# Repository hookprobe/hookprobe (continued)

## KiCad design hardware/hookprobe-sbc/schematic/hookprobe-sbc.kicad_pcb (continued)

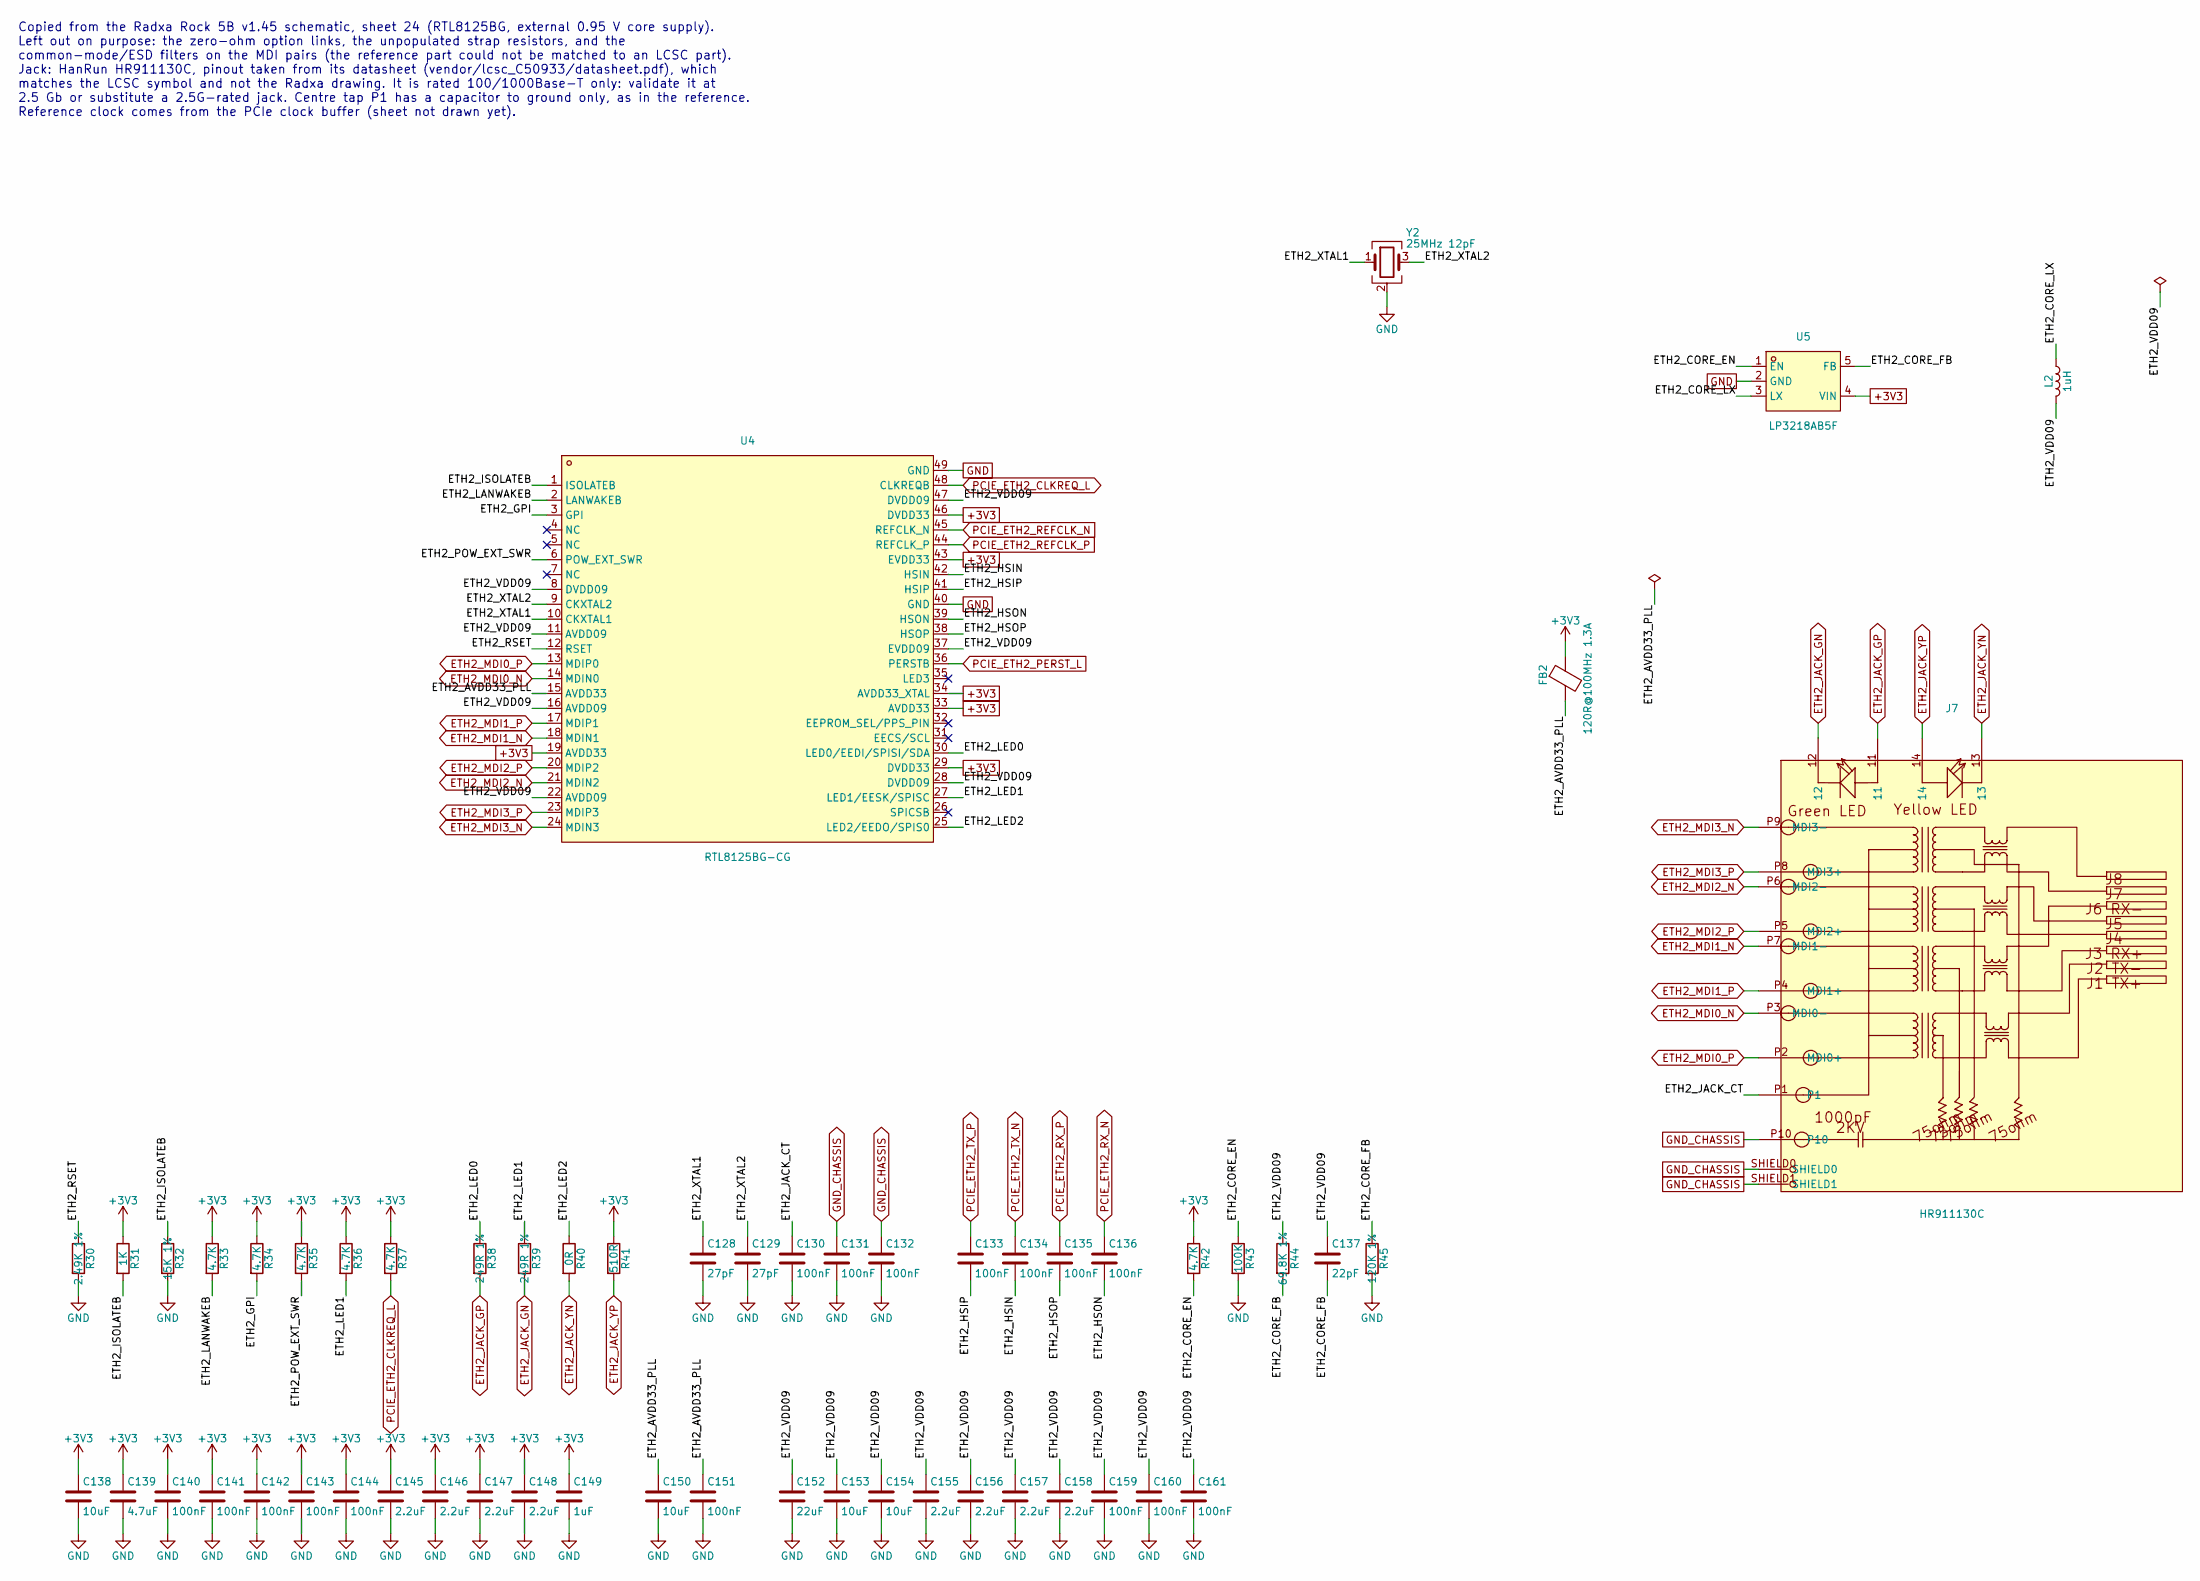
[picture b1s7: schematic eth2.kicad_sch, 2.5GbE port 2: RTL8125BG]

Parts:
C128, C129: 27pF; C_0402_1005Metric
C130, C131, C132, C133, C134, C135, C136, C140, C141, C142, C143, C144, C151, C159, C160, C161: 100nF; C_0402_1005Metric
C137: 22pF; C_0402_1005Metric
C138, C150, C153, C154: 10uF; C_0805_2012Metric
C139: 4.7uF; C_0805_2012Metric
C145, C146, C147, C148, C155, C156, C157, C158: 2.2uF; C_0402_1005Metric
C149: 1uF; C_0402_1005Metric
C152: 22uF; C_0805_2012Metric
FB2: 120R@100MHz 1.3A; L_0402_1005Metric; Part UPZ1005D121-1R3TF
J7: HR911130C; RJ45-TH_HR911130C; LCSC C50933
L2: 1uH; L_0805_2012Metric
R30: 2.49K 1%; R_0402_1005Metric
R31: 1K; R_0402_1005Metric
R32: 15K 1%; R_0402_1005Metric
R33, R34, R35, R36, R37, R42: 4.7K; R_0402_1005Metric
R38, R39: 249R 1%; R_0402_1005Metric
R40: 0R; R_0402_1005Metric
R41: 510R; R_0402_1005Metric
R43: 100K; R_0402_1005Metric
R44: 69.8K 1%; R_0402_1005Metric
R45: 120K 1%; R_0402_1005Metric
U4: RTL8125BG-CG; TQFN-48_L6.0-W6.0-P0.40-BL-EP4.5; LCSC C3013605
U5: LP3218AB5F; SOT-23-5_L2.9-W1.6-P0.95-LS2.8-BR; LCSC C517210
Y2: 25MHz 12pF; Crystal_SMD_3225-4Pin_3.2x2.5mm

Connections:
+3V3: C138.1, C139.1, C140.1, C141.1, C142.1, C143.1, C144.1, C145.1, C146.1, C147.1, C148.1, C149.1, FB2.1, R31.1, R33.1, R34.1, R35.1, R36.1, R37.1, R41.1, R42.1, U4.19 (AVDD33), U4.29 (DVDD33), U4.33 (AVDD33), U4.34 (AVDD33_XTAL), U4.43 (EVDD33), U4.46 (DVDD33), U5.4 (VIN); also elsewhere on the board
/2.5GbE port 2: RTL8125BG/ETH2_AVDD33_PLL: C150.1, C151.1, FB2.2, U4.15 (AVDD33)
/2.5GbE port 2: RTL8125BG/ETH2_CORE_EN: R42.2, R43.1, U5.1 (EN)
/2.5GbE port 2: RTL8125BG/ETH2_CORE_FB: C137.2, R44.2, R45.1, U5.5 (FB)
/2.5GbE port 2: RTL8125BG/ETH2_CORE_LX: L2.1, U5.3 (LX)
/2.5GbE port 2: RTL8125BG/ETH2_GPI: R34.2, U4.3 (GPI)
/2.5GbE port 2: RTL8125BG/ETH2_HSIN: C134.2, U4.42 (HSIN)
/2.5GbE port 2: RTL8125BG/ETH2_HSIP: C133.2, U4.41 (HSIP)
/2.5GbE port 2: RTL8125BG/ETH2_HSON: C136.2, U4.39 (HSON)
/2.5GbE port 2: RTL8125BG/ETH2_HSOP: C135.2, U4.38 (HSOP)
/2.5GbE port 2: RTL8125BG/ETH2_ISOLATEB: R31.2, R32.1, U4.1 (ISOLATEB)
/2.5GbE port 2: RTL8125BG/ETH2_JACK_CT: C130.1, J7.P1
/2.5GbE port 2: RTL8125BG/ETH2_LANWAKEB: R33.2, U4.2 (LANWAKEB)
/2.5GbE port 2: RTL8125BG/ETH2_LED0: R38.1, U4.30 (LED0/EEDI/SPISI/SDA)
/2.5GbE port 2: RTL8125BG/ETH2_LED1: R36.2, R39.1, U4.27 (LED1/EESK/SPISC)
/2.5GbE port 2: RTL8125BG/ETH2_LED2: R40.1, U4.25 (LED2/EEDO/SPIS0)
/2.5GbE port 2: RTL8125BG/ETH2_POW_EXT_SWR: R35.2, U4.6 (POW_EXT_SWR)
/2.5GbE port 2: RTL8125BG/ETH2_RSET: R30.1, U4.12 (RSET)
/2.5GbE port 2: RTL8125BG/ETH2_VDD09: C137.1, C152.1, C153.1, C154.1, C155.1, C156.1, C157.1, C158.1, C159.1, C160.1, C161.1, L2.2, R44.1, U4.8 (DVDD09), U4.11 (AVDD09), U4.16 (AVDD09), U4.22 (AVDD09), U4.28 (DVDD09), U4.37 (EVDD09), U4.47 (DVDD09)
/2.5GbE port 2: RTL8125BG/ETH2_XTAL1: C128.1, U4.10 (CKXTAL1), Y2.1
/2.5GbE port 2: RTL8125BG/ETH2_XTAL2: C129.1, U4.9 (CKXTAL2), Y2.3
ETH2_JACK_GN: J7.12, R39.2
ETH2_JACK_GP: J7.11, R38.2
ETH2_JACK_YN: J7.13, R40.2
ETH2_JACK_YP: J7.14, R41.2
ETH2_MDI0_N: J7.P3 (MDI0-), U4.14 (MDIN0)
ETH2_MDI0_P: J7.P2 (MDI0+), U4.13 (MDIP0)
ETH2_MDI1_N: J7.P7 (MDI1-), U4.18 (MDIN1)
ETH2_MDI1_P: J7.P4 (MDI1+), U4.17 (MDIP1)
ETH2_MDI2_N: J7.P6 (MDI2-), U4.21 (MDIN2)
ETH2_MDI2_P: J7.P5 (MDI2+), U4.20 (MDIP2)
ETH2_MDI3_N: J7.P9 (MDI3-), U4.24 (MDIN3)
ETH2_MDI3_P: J7.P8 (MDI3+), U4.23 (MDIP3)
GND: C128.2, C129.2, C130.2, C131.2, C132.2, C138.2, C139.2, C140.2, C141.2, C142.2, C143.2, C144.2, C145.2, C146.2, C147.2, C148.2, C149.2, C150.2, C151.2, C152.2, C153.2, C154.2, C155.2, C156.2, C157.2, C158.2, C159.2, C160.2, C161.2, R30.2, R32.2, R43.2, R45.2, U4.40 (GND), U4.49 (GND), U5.2 (GND), Y2.2 (G), Y2.4 (G); also elsewhere on the board
GND_CHASSIS: C131.1, C132.1, J7.P10, J7.SHIELD0, J7.SHIELD1; also elsewhere on the board
PCIE_ETH2_CLKREQ_L: R37.2, U4.48 (CLKREQB); also elsewhere on the board
PCIE_ETH2_PERST_L: U4.36 (PERSTB); also elsewhere on the board
PCIE_ETH2_REFCLK_N: U4.45 (REFCLK_N); also elsewhere on the board
PCIE_ETH2_REFCLK_P: U4.44 (REFCLK_P); also elsewhere on the board
PCIE_ETH2_RX_N: C136.1; also elsewhere on the board
PCIE_ETH2_RX_P: C135.1; also elsewhere on the board
PCIE_ETH2_TX_N: C134.1; also elsewhere on the board
PCIE_ETH2_TX_P: C133.1; also elsewhere on the board

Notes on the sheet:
Copied from the Radxa Rock 5B v1.45 schematic, sheet 24 (RTL8125BG, external 0.95 V core supply). Left out on purpose: the zero-ohm option links, the unpopulated strap resistors, and the common-mode/ESD filters on the MDI pairs (the reference part could not be matched to an LCSC part). Jack: HanRun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

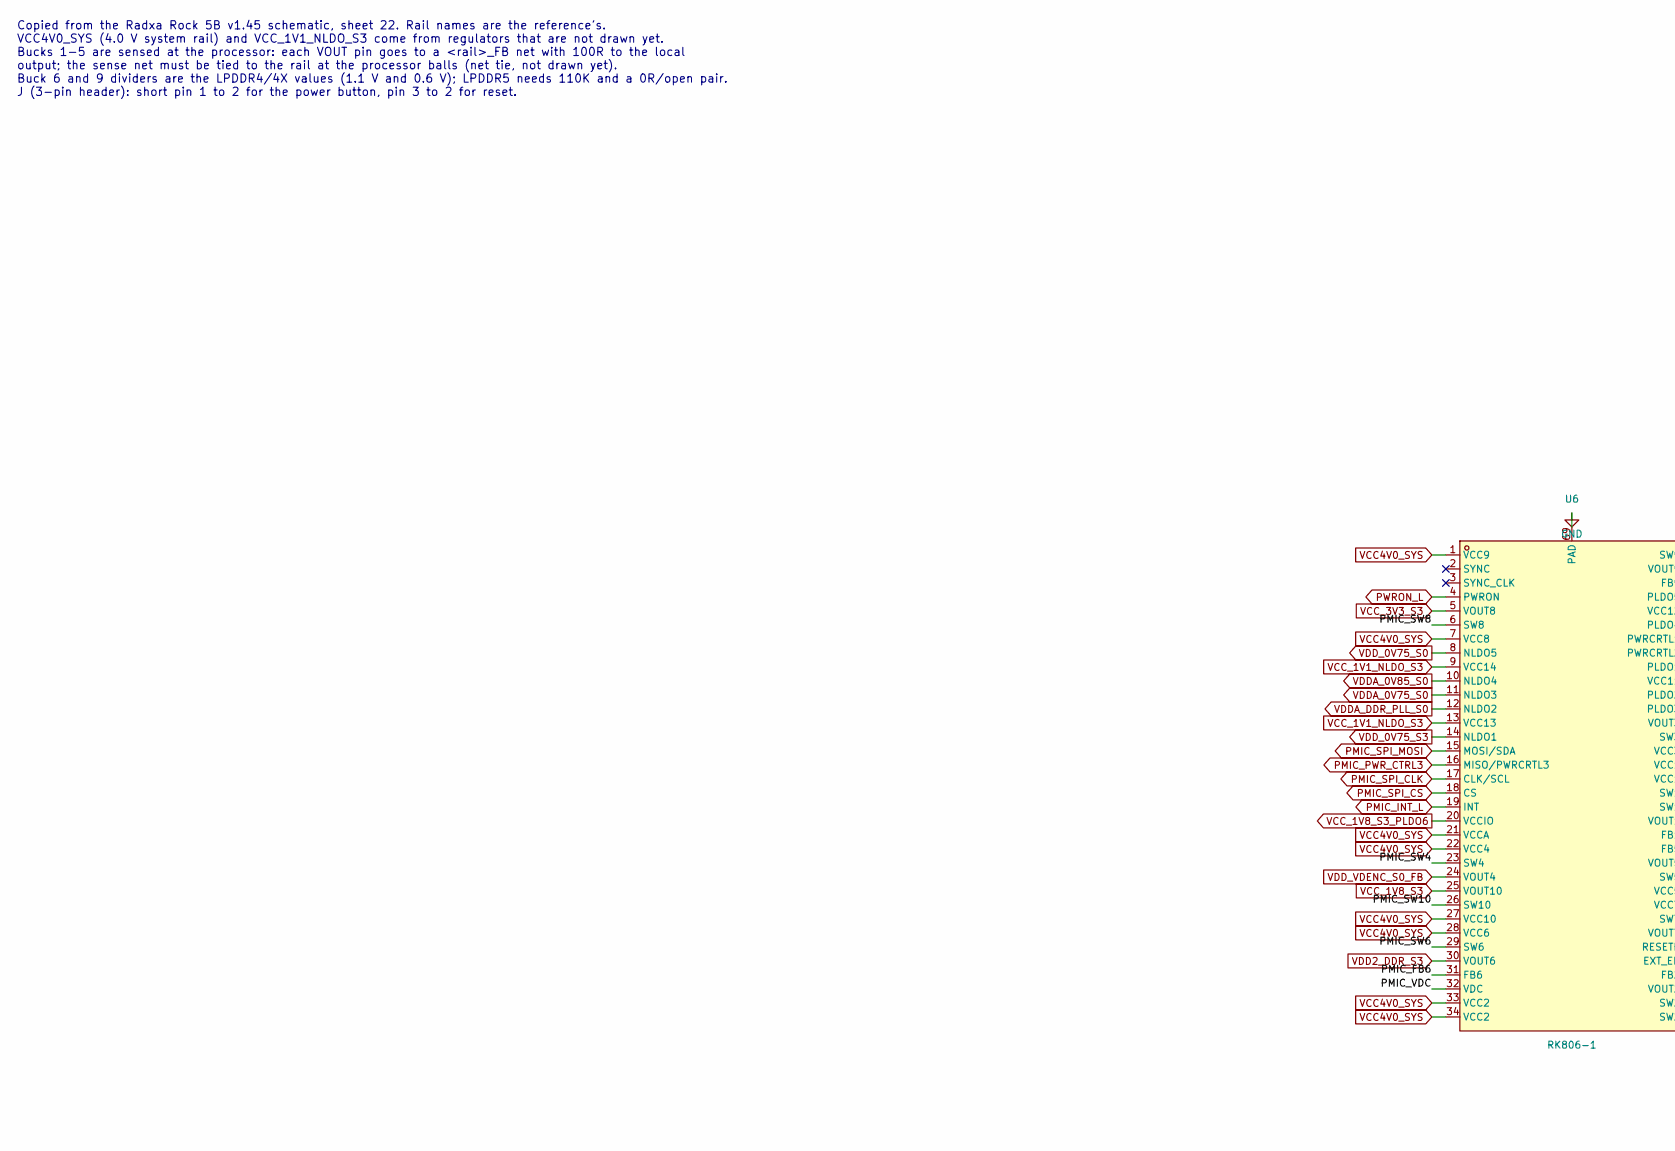
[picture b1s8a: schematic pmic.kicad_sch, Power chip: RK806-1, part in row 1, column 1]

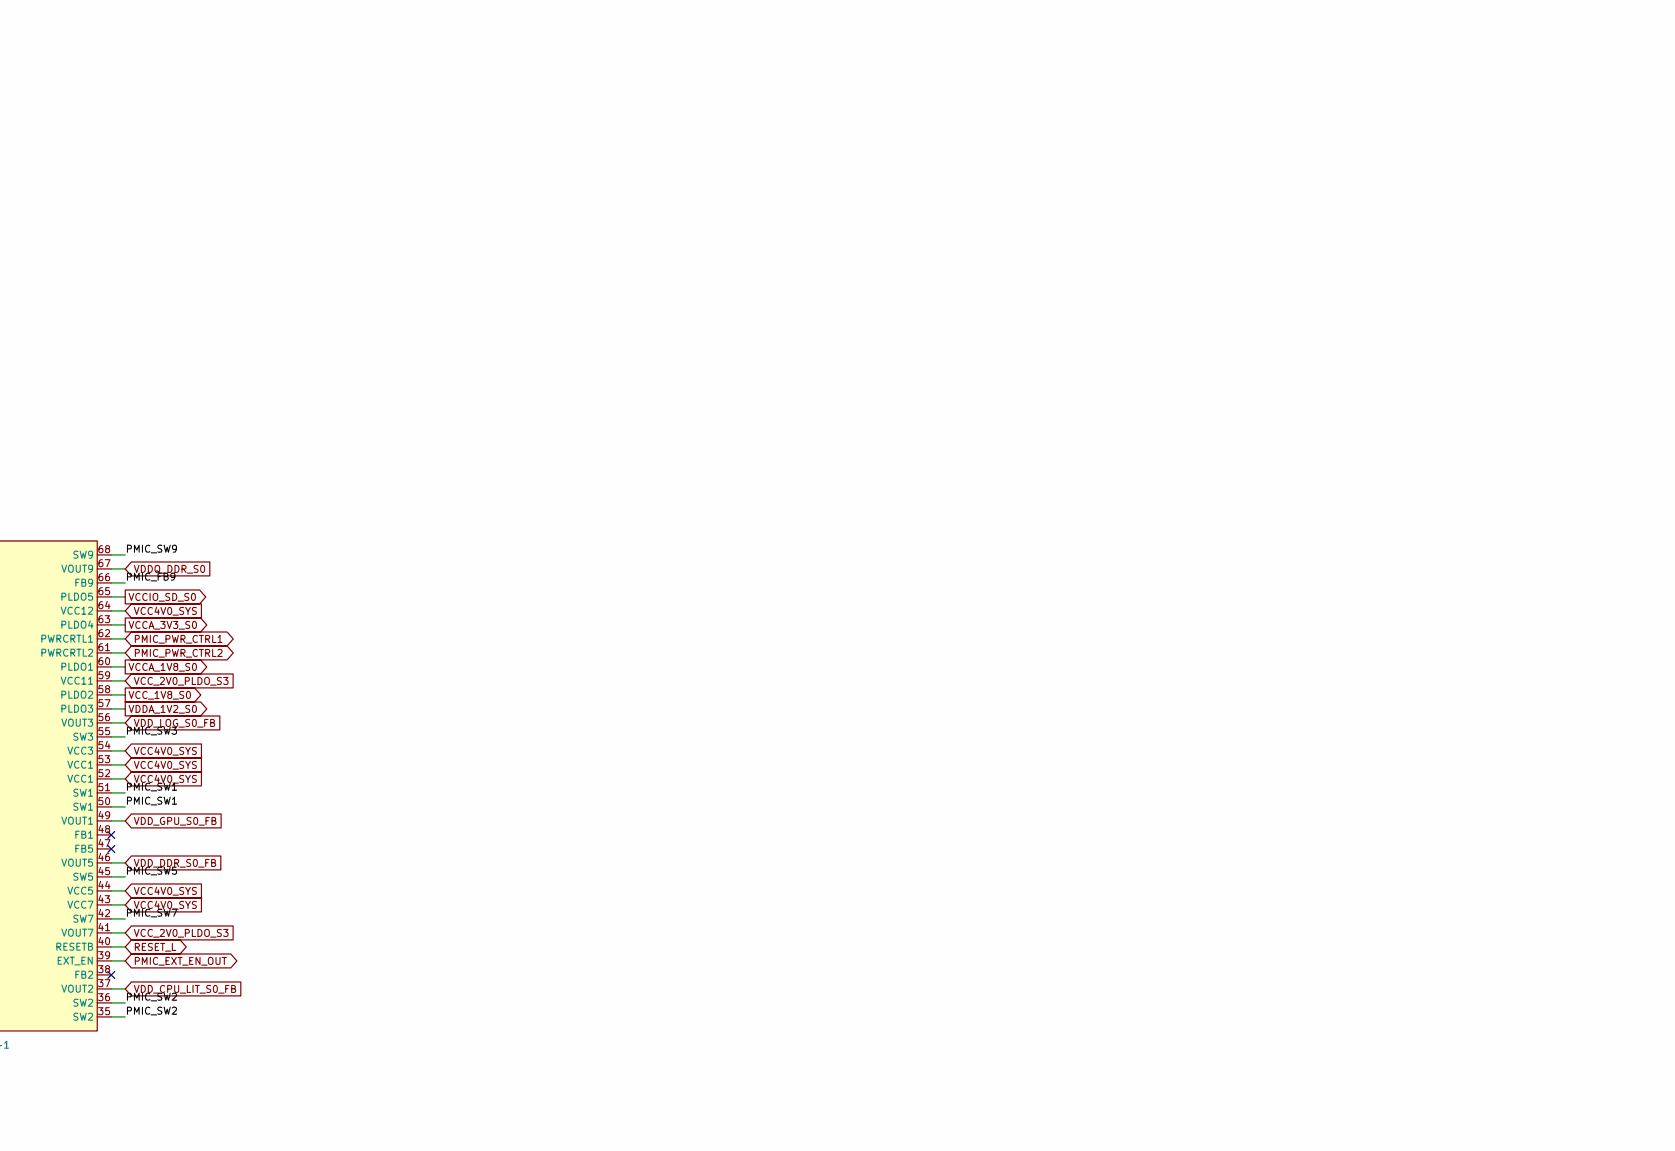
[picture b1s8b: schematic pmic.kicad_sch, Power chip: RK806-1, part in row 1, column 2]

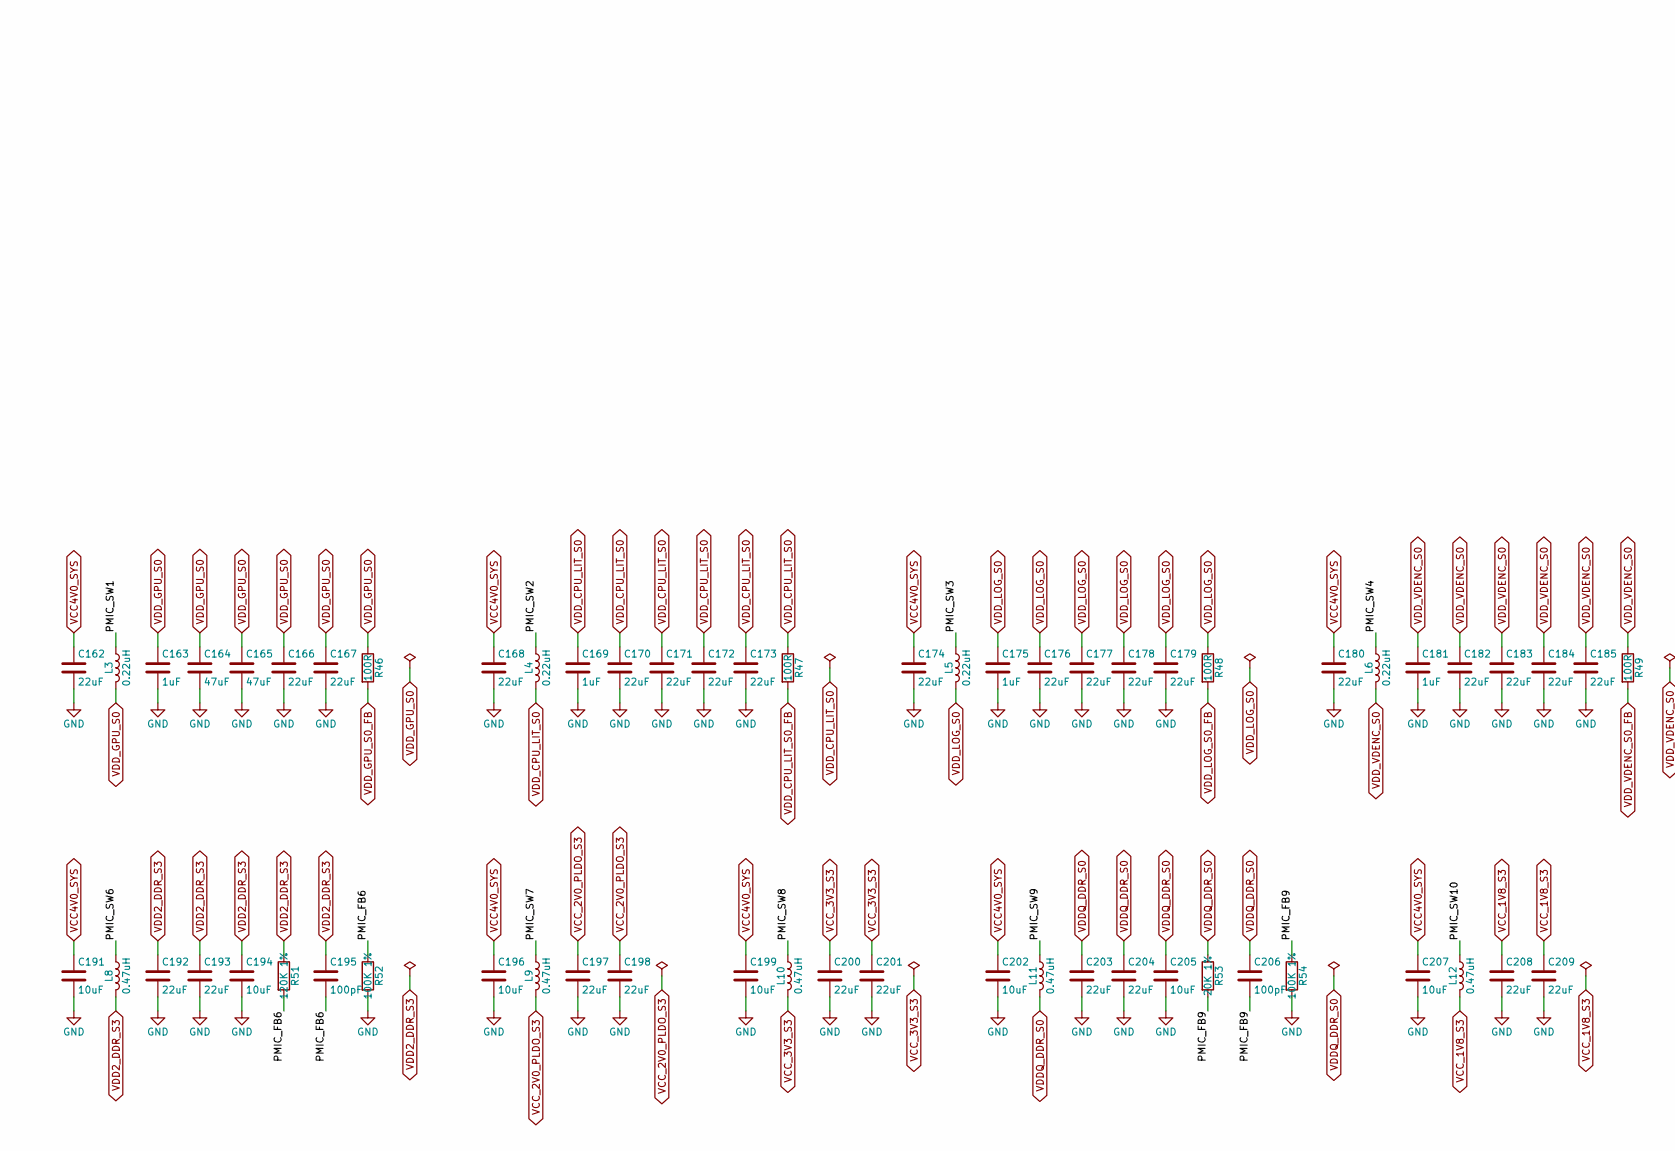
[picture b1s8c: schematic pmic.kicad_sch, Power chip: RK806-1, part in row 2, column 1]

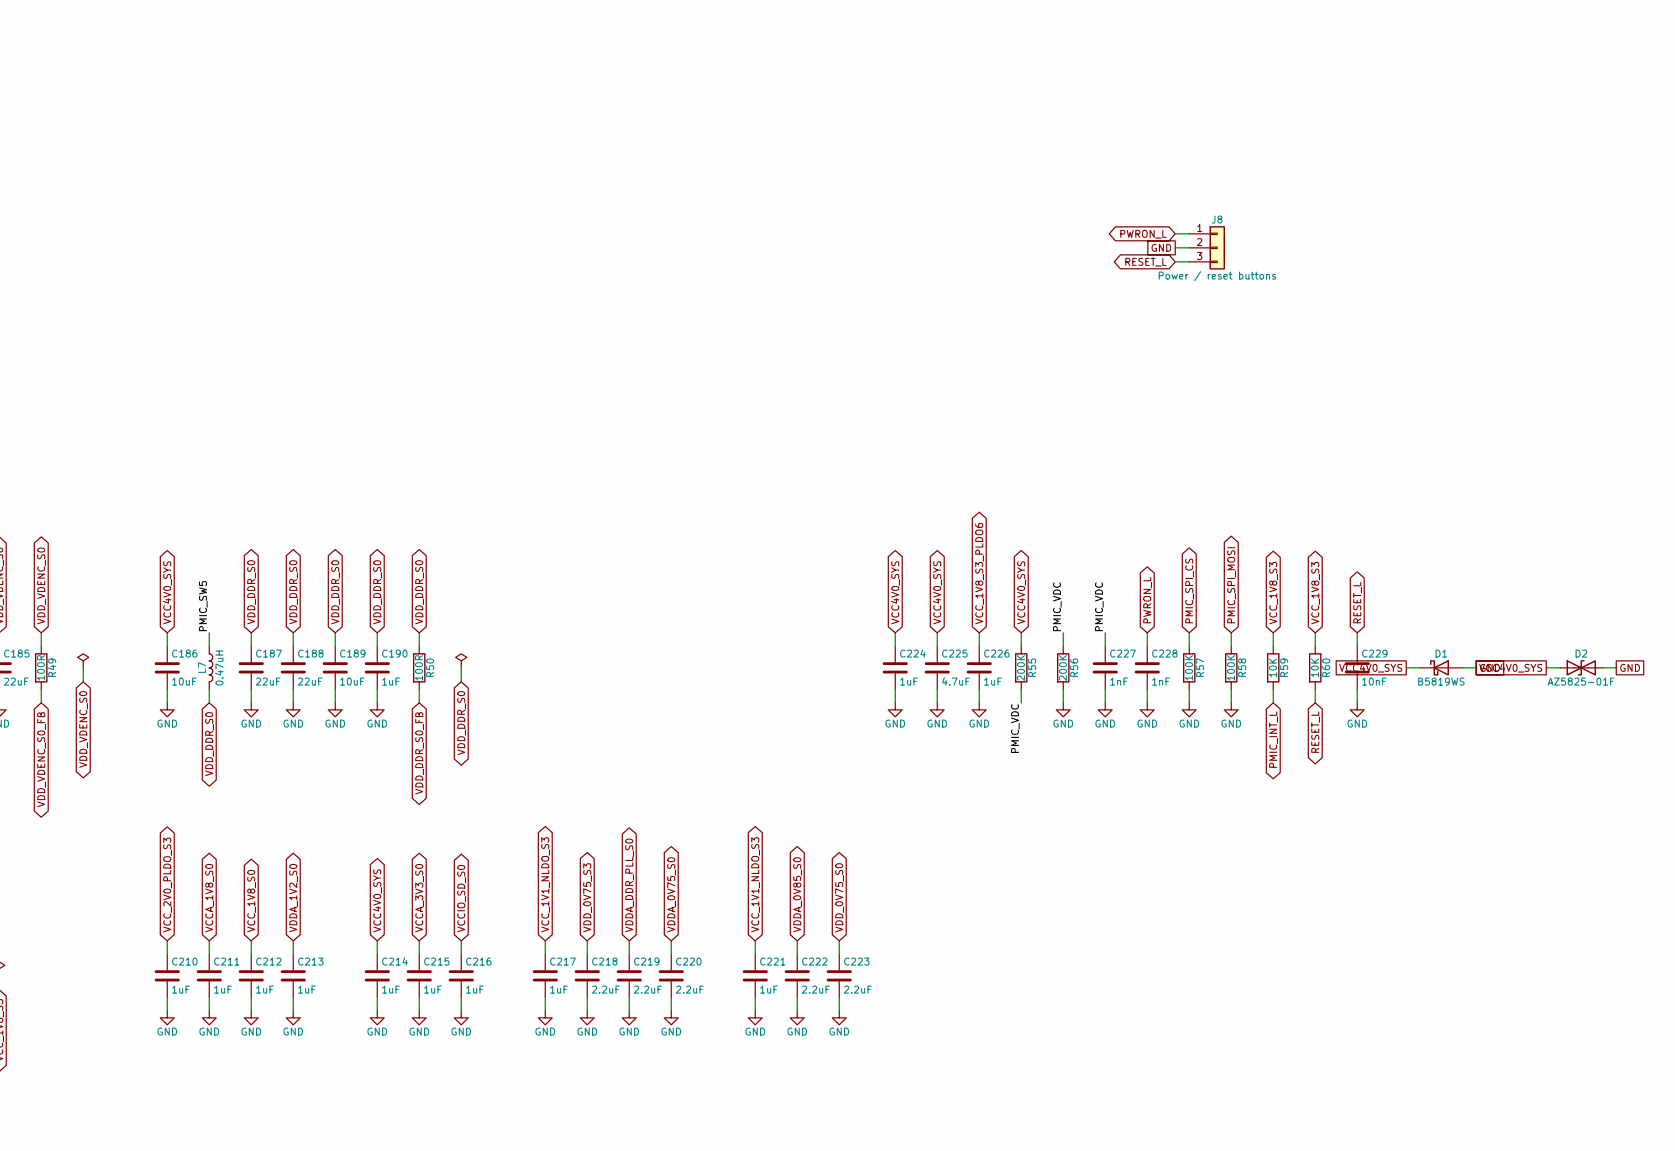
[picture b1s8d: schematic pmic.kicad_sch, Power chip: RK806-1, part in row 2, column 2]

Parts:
C162, C168, C174, C180: 22uF; C_0805_2012Metric
C163, C169, C175, C181, C190, C210, C211, C212, C213, C214, C215, C216, C217, C221, C224, C226: 1uF; C_0402_1005Metric
C164, C165: 47uF; C_0805_2012Metric
C166, C167, C170, C171, C172, C173, C176, C177, C178, C179, C182, C183, C184, C185, C187, C188, C192, C193, C197, C198, C200, C201, C203, C204, C208, C209: 22uF; C_0603_1608Metric
C186, C189, C191, C194, C196, C199, C202, C205, C207: 10uF; C_0603_1608Metric
C195, C206: 100pF; C_0402_1005Metric
C218, C219, C220, C222, C223: 2.2uF; C_0402_1005Metric
C225: 4.7uF; C_0402_1005Metric
C227, C228: 1nF; C_0402_1005Metric
C229: 10nF; C_0402_1005Metric
D1: B5819WS; D_SOD-323
D2: AZ5825-01F; D_0402_1005Metric
J8: Power / reset buttons; PinHeader_1x03_P2.54mm_Vertical
L3, L4, L5, L6: 0.22uH; L_1210_3225Metric
L7, L8, L9, L10, L11, L12: 0.47uH; L_1210_3225Metric
R46, R47, R48, R49, R50: 100R; R_0402_1005Metric
R51: 120K 1%; R_0402_1005Metric
R52, R54: 100K 1%; R_0402_1005Metric
R53: 20K 1%; R_0402_1005Metric
R55, R56: 200K; R_0402_1005Metric
R57, R58: 100K; R_0402_1005Metric
R59, R60: 10K; R_0402_1005Metric
U6: RK806-1; QFN-68_L7.0-W7.0-P0.35-BL-EP5.5; LCSC C5156483

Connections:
/Power chip: RK806-1/PMIC_FB6: C195.2, R51.2, R52.1, U6.31 (FB6)
/Power chip: RK806-1/PMIC_FB9: C206.2, R53.2, R54.1, U6.66 (FB9)
/Power chip: RK806-1/PMIC_SW1: L3.1, U6.50 (SW1), U6.51 (SW1)
/Power chip: RK806-1/PMIC_SW2: L4.1, U6.35 (SW2), U6.36 (SW2)
/Power chip: RK806-1/PMIC_SW3: L5.1, U6.55 (SW3)
/Power chip: RK806-1/PMIC_SW4: L6.1, U6.23 (SW4)
/Power chip: RK806-1/PMIC_SW5: L7.1, U6.45 (SW5)
/Power chip: RK806-1/PMIC_SW6: L8.1, U6.29 (SW6)
/Power chip: RK806-1/PMIC_SW7: L9.1, U6.42 (SW7)
/Power chip: RK806-1/PMIC_SW8: L10.1, U6.6 (SW8)
/Power chip: RK806-1/PMIC_SW9: L11.1, U6.68 (SW9)
/Power chip: RK806-1/PMIC_SW10: L12.1, U6.26 (SW10)
/Power chip: RK806-1/PMIC_VDC: C227.1, R55.2, R56.1, U6.32 (VDC)
GND: C162.2, C163.2, C164.2, C165.2, C166.2, C167.2, C168.2, C169.2, C170.2, C171.2, C172.2, C173.2, C174.2, C175.2, C176.2, C177.2, C178.2, C179.2, C180.2, C181.2, C182.2, C183.2, C184.2, C185.2, C186.2, C187.2, C188.2, C189.2, C190.2, C191.2, C192.2, C193.2, C194.2, C196.2, C197.2, C198.2, C199.2, C200.2, C201.2, C202.2, C203.2, C204.2, C205.2, C207.2, C208.2, C209.2, C210.2, C211.2, C212.2, C213.2, C214.2, C215.2, C216.2, C217.2, C218.2, C219.2, C220.2, C221.2, C222.2, C223.2, C224.2, C225.2, C226.2, C227.2, C228.2, C229.2, D1.2 (A), D2.2 (A2), J8.2, R52.2, R54.2, R56.2, R57.2, R58.2, U6.69 (PAD); also elsewhere on the board
PMIC_EXT_EN_OUT: U6.39 (EXT_EN); also elsewhere on the board
PMIC_INT_L: R59.2, U6.19 (INT); also elsewhere on the board
PMIC_PWR_CTRL1: U6.62 (PWRCRTL1); also elsewhere on the board
PMIC_PWR_CTRL2: U6.61 (PWRCRTL2); also elsewhere on the board
PMIC_PWR_CTRL3: U6.16 (MISO/PWRCRTL3); also elsewhere on the board
PMIC_SPI_CLK: U6.17 (CLK/SCL); also elsewhere on the board
PMIC_SPI_CS: R57.1, U6.18 (CS); also elsewhere on the board
PMIC_SPI_MOSI: R58.1, U6.15 (MOSI/SDA); also elsewhere on the board
PWRON_L: C228.1, J8.1, U6.4 (PWRON)
RESET_L: C229.1, J8.3, R60.2, U6.40 (RESETB); also elsewhere on the board
VCC4V0_SYS: C162.1, C168.1, C174.1, C180.1, C186.1, C191.1, C196.1, C199.1, C202.1, C207.1, C214.1, C224.1, C225.1, D1.1 (K), D2.1 (A1), R55.1, U6.1 (VCC9), U6.7 (VCC8), U6.21 (VCCA), U6.22 (VCC4), U6.27 (VCC10), U6.28 (VCC6), U6.33 (VCC2), U6.34 (VCC2), U6.43 (VCC7), U6.44 (VCC5), U6.52 (VCC1), U6.53 (VCC1), U6.54 (VCC3), U6.64 (VCC12); also elsewhere on the board
VCCA_1V8_S0: C211.1, U6.60 (PLDO1); also elsewhere on the board
VCCA_3V3_S0: C215.1, U6.63 (PLDO4); also elsewhere on the board
VCCIO_SD_S0: C216.1, U6.65 (PLDO5); also elsewhere on the board
VCC_1V1_NLDO_S3: C217.1, C221.1, U6.9 (VCC14), U6.13 (VCC13); also elsewhere on the board
VCC_1V8_S0: C212.1, U6.58 (PLDO2); also elsewhere on the board
VCC_1V8_S3: C208.1, C209.1, L12.2, R59.1, R60.1, U6.25 (VOUT10); also elsewhere on the board
VCC_1V8_S3_PLDO6: C226.1, U6.20 (VCCIO)
VCC_2V0_PLDO_S3: C197.1, C198.1, C210.1, L9.2, U6.41 (VOUT7), U6.59 (VCC11)
VCC_3V3_S3: C200.1, C201.1, L10.2, U6.5 (VOUT8); also elsewhere on the board
VDD2_DDR_S3: C192.1, C193.1, C194.1, C195.1, L8.2, R51.1, U6.30 (VOUT6); also elsewhere on the board
VDDA_0V75_S0: C220.1, U6.11 (NLDO3); also elsewhere on the board
VDDA_0V85_S0: C222.1, U6.10 (NLDO4); also elsewhere on the board
VDDA_1V2_S0: C213.1, U6.57 (PLDO3); also elsewhere on the board
VDDA_DDR_PLL_S0: C219.1, U6.12 (NLDO2); also elsewhere on the board
VDDQ_DDR_S0: C203.1, C204.1, C205.1, C206.1, L11.2, R53.1, U6.67 (VOUT9); also elsewhere on the board
VDD_0V75_S0: C223.1, U6.8 (NLDO5); also elsewhere on the board
VDD_0V75_S3: C218.1, U6.14 (NLDO1); also elsewhere on the board
VDD_CPU_LIT_S0: C169.1, C170.1, C171.1, C172.1, C173.1, L4.2, R47.1; also elsewhere on the board
VDD_CPU_LIT_S0_FB: R47.2, U6.37 (VOUT2); also elsewhere on the board
VDD_DDR_S0: C187.1, C188.1, C189.1, C190.1, L7.2, R50.1; also elsewhere on the board
VDD_DDR_S0_FB: R50.2, U6.46 (VOUT5); also elsewhere on the board
VDD_GPU_S0: C163.1, C164.1, C165.1, C166.1, C167.1, L3.2, R46.1; also elsewhere on the board
VDD_GPU_S0_FB: R46.2, U6.49 (VOUT1); also elsewhere on the board
VDD_LOG_S0: C175.1, C176.1, C177.1, C178.1, C179.1, L5.2, R48.1; also elsewhere on the board
VDD_LOG_S0_FB: R48.2, U6.56 (VOUT3); also elsewhere on the board
VDD_VDENC_S0: C181.1, C182.1, C183.1, C184.1, C185.1, L6.2, R49.1; also elsewhere on the board
VDD_VDENC_S0_FB: R49.2, U6.24 (VOUT4); also elsewhere on the board

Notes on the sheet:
Copied from the Radxa Rock 5B v1.45 schematic, sheet 22. Rail names are the reference's. VCC4V0_SYS (4.0 V system rail) and VCC_1V1_NLDO_S3 come from regulators that are not drawn yet. Bucks 1-5 are sensed at the processor: each VOUT pin goes to a <rail>_FB net with 100R to the local output; the se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

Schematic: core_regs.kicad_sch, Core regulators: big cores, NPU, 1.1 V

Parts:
C230, C231, C238, C239, C246, C247: 22uF; C_0805_2012Metric
C232, C240, C248: 1uF; C_0402_1005Metric
C233, C234, C235, C236, C237, C241, C242, C243, C244, C245, C251, C252, C253, C254, C257: 22uF; C_0603_1608Metric
C249, C250: 47uF; C_0805_2012Metric
C255, C259, C260: 10uF; C_0603_1608Metric
C256: 100pF; C_0402_1005Metric
C258: 100nF; C_0402_1005Metric
FB3: 120R@100MHz; L_0603_1608Metric
L13, L14, L15: 0.22uH; L_1210_3225Metric
L16: 2.2uH; L_1210_3225Metric
R61, R62, R63: 100R; R_0402_1005Metric
R64, R70: 100K; R_0402_1005Metric
R65: 120K; R_0402_1005Metric
R66, R69: 10K; R_0402_1005Metric
R67: 100K 1%; R_0402_1005Metric
R68: 120K 1%; R_0402_1005Metric
R71: 4.7K; R_0402_1005Metric
U7, U9: RK860-2; WLCSP-20_L2.0-W1.6-R5-C4-P0.40-TL; LCSC C5156489
U8: RK860-3; WLCSP-20_L2.0-W1.6-R5-C4-P0.40-TL; LCSC C5156487
U10: SY8089AAAC; SOT-23-5_L3.0-W1.7-P0.95-LS2.8-BR; LCSC C78988
U11: SY6280AAC; SOT-23-5_L3.0-W1.7-P0.95-LS2.8-BL; LCSC C55136

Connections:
/Core regulators: big cores, NPU, 1.1 V/BIG_NPU_EN: R64.2, R65.1, U7.A2 (EN), U8.A2 (EN), U9.A2 (EN)
/Core regulators: big cores, NPU, 1.1 V/SW_VDD_CPU_BIG0_S0: L13.1, U7.D3 (LX), U7.D4 (LX), U7.E3 (LX), U7.E4 (LX)
/Core regulators: big cores, NPU, 1.1 V/SW_VDD_CPU_BIG1_S0: L14.1, U8.D3 (LX), U8.D4 (LX), U8.E3 (LX), U8.E4 (LX)
/Core regulators: big cores, NPU, 1.1 V/SW_VDD_NPU_S0: L15.1, U9.D3 (LX), U9.D4 (LX), U9.E3 (LX), U9.E4 (LX)
/Core regulators: big cores, NPU, 1.1 V/V1V1_EN: R66.2, U10.1 (EN)
/Core regulators: big cores, NPU, 1.1 V/V1V1_FB: C256.2, R67.2, R68.1, U10.5 (FB)
/Core regulators: big cores, NPU, 1.1 V/V1V1_LX: L16.1, U10.3 (LX)
/Core regulators: big cores, NPU, 1.1 V/V3V3S0_EN: R69.2, R70.1, U11.4 (EN)
/Core regulators: big cores, NPU, 1.1 V/V3V3S0_ISET: R71.1, U11.3 (ISET)
CPU_BIG0_VSEL: U7.A1 (VSEL); also elsewhere on the board
CPU_BIG1_VSEL: U8.A1 (VSEL); also elsewhere on the board
GND: C230.2, C231.2, C232.2, C233.2, C234.2, C235.2, C236.2, C237.2, C238.2, C239.2, C240.2, C241.2, C242.2, C243.2, C244.2, C245.2, C246.2, C247.2, C248.2, C249.2, C250.2, C251.2, C252.2, C253.2, C254.2, C255.2, C257.2, C258.2, C259.2, C260.2, R65.2, R68.2, R70.2, R71.2, U7.B2 (GND), U7.B3 (GND), U7.B4 (AGND), U7.C1 (GND), U7.C2 (GND), U7.C3 (GND), U7.C4 (GND), U8.B2 (GND), U8.B3 (GND), U8.B4 (AGND), U8.C1 (GND), U8.C2 (GND), U8.C3 (GND), U8.C4 (GND), U9.B2 (GND), U9.B3 (GND), U9.B4 (AGND), U9.C1 (GND), U9.C2 (GND), U9.C3 (GND), U9.C4 (GND), U10.2 (GND), U11.2 (GND); also elsewhere on the board
I2C0_SCL_M2: U7.A3 (SCL), U8.A3 (SCL); also elsewhere on the board
I2C0_SDA_M2: U7.B1 (SDA), U8.B1 (SDA); also elsewhere on the board
I2C1_SCL_M2: U9.A3 (SCL); also elsewhere on the board
I2C1_SDA_M2: U9.B1 (SDA); also elsewhere on the board
NPU_VSEL: U9.A1 (VSEL); also elsewhere on the board
PMIC_EXT_EN_OUT: R66.1; also elsewhere on the board
VCC4V0_SYS: C230.1, C231.1, C238.1, C239.1, C246.1, C247.1, C255.1, U7.D1 (VIN), U7.D2 (VIN), U7.E1 (VIN), U7.E2 (VIN), U8.D1 (VIN), U8.D2 (VIN), U8.E1 (VIN), U8.E2 (VIN), U9.D1 (VIN), U9.D2 (VIN), U9.E1 (VIN), U9.E2 (VIN), U10.4 (IN); also elsewhere on the board
VCCA_3V3_S0: R69.1; also elsewhere on the board
VCC_1V1_NLDO_S3: C256.1, C257.1, C258.1, L16.2, R67.1; also elsewhere on the board
VCC_3V3_S0: C260.1, U11.1 (OUT); also elsewhere on the board
VCC_3V3_S3: C259.1, R64.1, U11.5 (IN); also elsewhere on the board
VDD_CPU_BIG0_S0: C232.1, C233.1, C234.1, C235.1, C236.1, C237.1, L13.2, R61.1; also elsewhere on the board
VDD_CPU_BIG0_S0_FB: R61.2, U7.A4 (VOUT); also elsewhere on the board
VDD_CPU_BIG1_MEM_S0: C254.1, FB3.2; also elsewhere on the board
VDD_CPU_BIG1_S0: C240.1, C241.1, C242.1, C243.1, C244.1, C245.1, FB3.1, L14.2, R62.1; also elsewhere on the board
VDD_CPU_BIG1_S0_FB: R62.2, U8.A4 (VOUT); also elsewhere on the board
VDD_NPU_S0: C248.1, C249.1, C250.1, C251.1, C252.1, C253.1, L15.2, R63.1; also elsewhere on the board
VDD_NPU_S0_FB: R63.2, U9.A4 (VOUT); also elsewhere on the board

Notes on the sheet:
Copied from the Radxa Rock 5B v1.45 schematic, sheet 23. U (RK860-2) big core 0 and U (RK860-3) big core 1 share I2C0; the NPU regulator (RK860-2) is on I2C1. Each VOUT pin is the remote sense input: it goes to <rail>_FB, tied to the rail at the processor. VCC_3V3_S0 switch: SY6280AAC in place of t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
